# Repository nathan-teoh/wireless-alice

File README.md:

# Wireless Alice

## I have no idea what i'm doing borther

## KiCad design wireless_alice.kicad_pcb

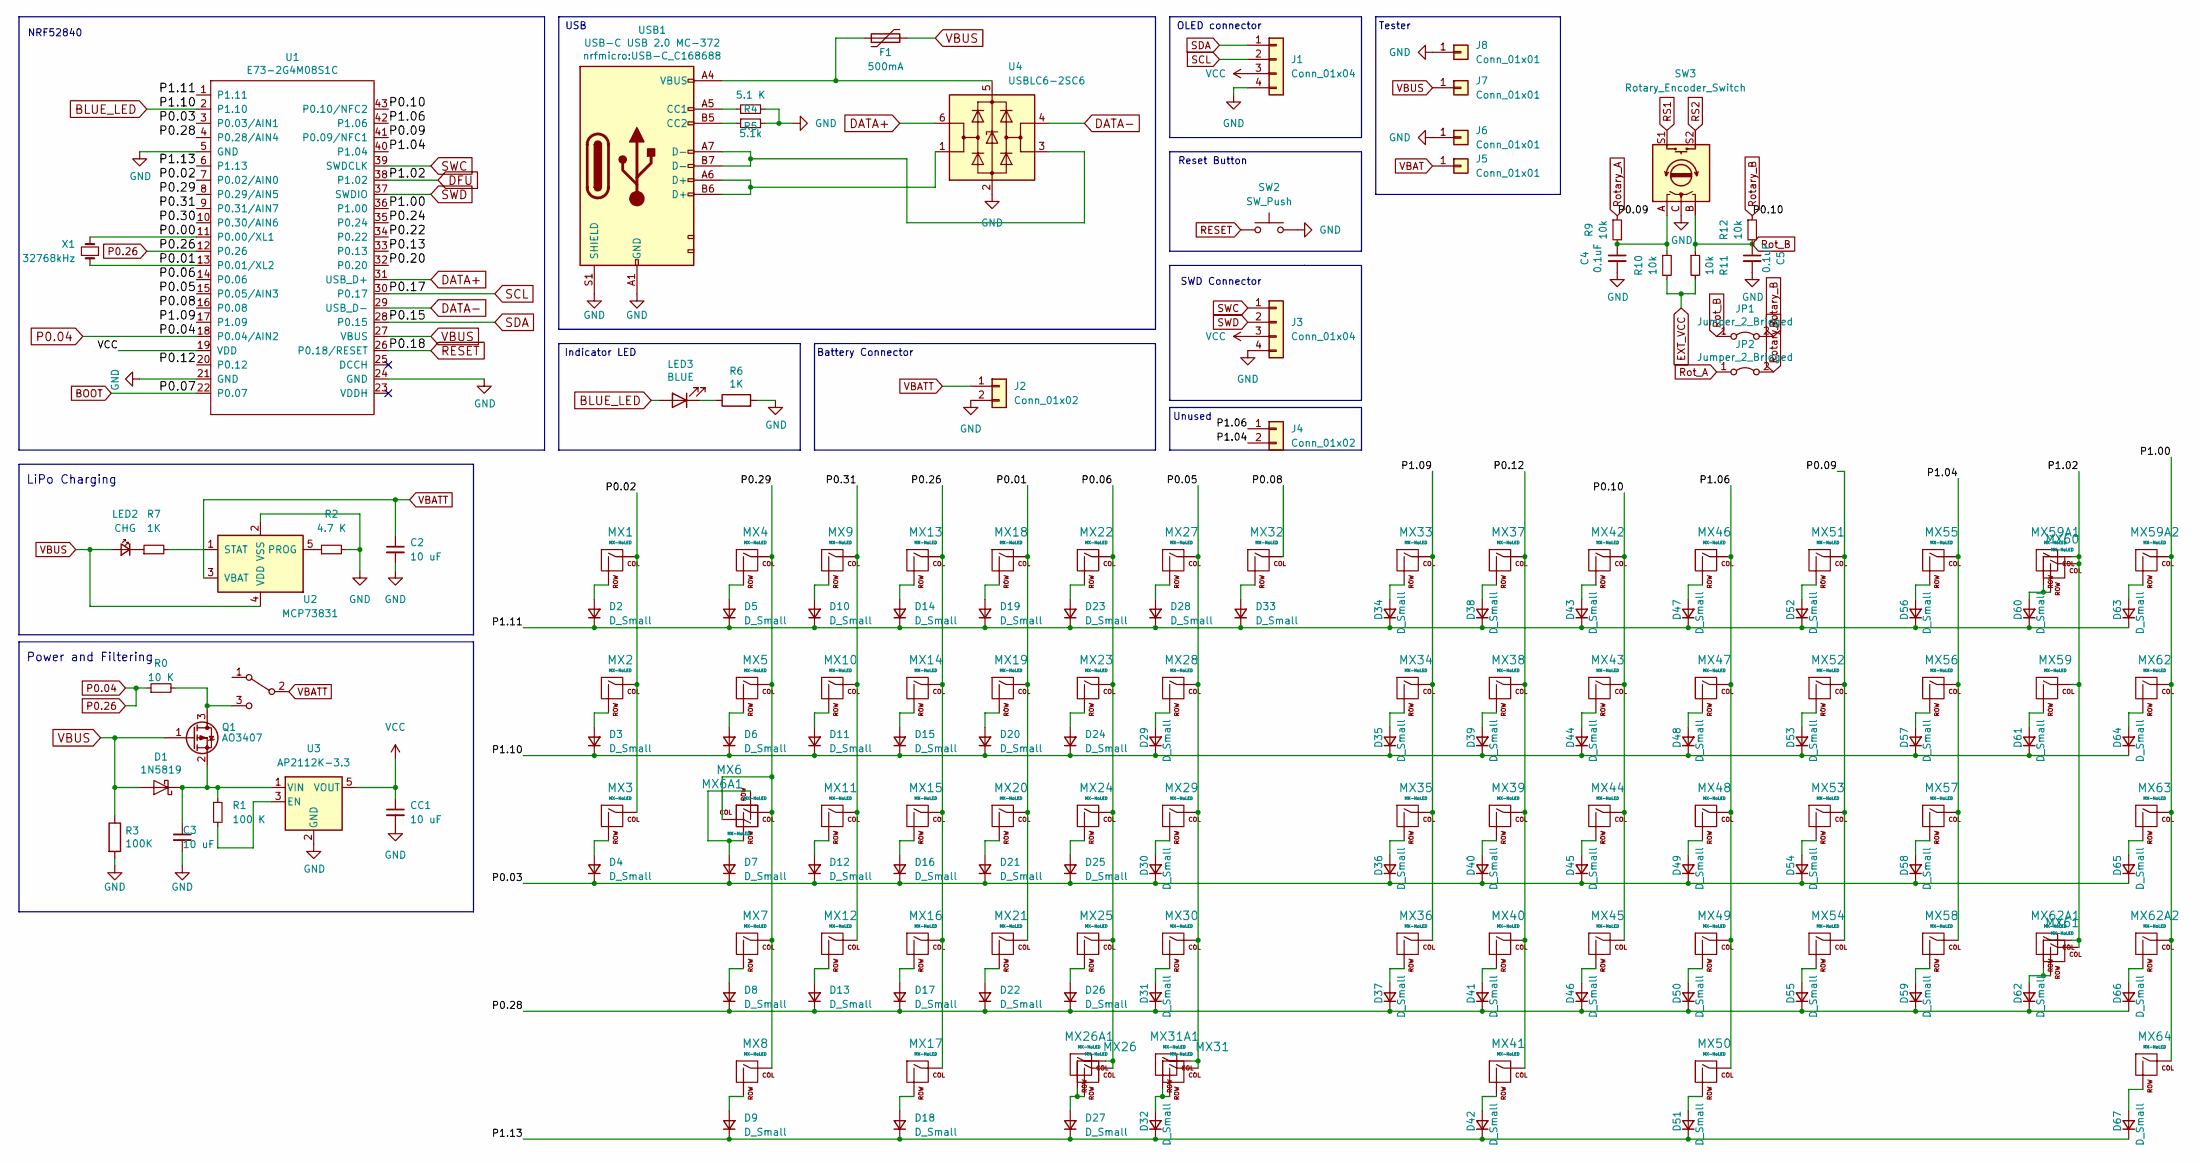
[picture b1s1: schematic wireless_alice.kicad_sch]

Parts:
C2, C3: 10 uF; C_Axial_L3.8mm_D2.6mm_P7.50mm_Horizontal
C4: 0.1uF; CP_Axial_L11.0mm_D6.0mm_P18.00mm_Horizontal; LCSC C49678
C5: 0.1uF; C_0805_2012Metric_Pad1.15x1.40mm_HandSolder; LCSC C49678
CC1: 10 uF; C_Axial_L3.8mm_D2.6mm_P7.50mm_Horizontal
D1: 1N5819; D_SOD-323F
D2, D3, D4, D5, D6, D7, D8, D9, D10, D11, D12, D13, D14, D15, D16, D17, D18, D19, D20, D21, D22, D23, D24, D25, D26, D27, D28, D29, D30, D31, D32, D33, D34, D35, D36, D37, D38, D39, D40, D41, D42, D43, D44, D45, D46, D47, D48, D49, D50, D51, D52, D53, D54, D55, D56, D57, D58, D59, D60, D61, D62, D63, D64, D65, D66, D67: D_Small; D_5W_P12.70mm_Horizontal
F1: 500mA; JST_EH_S4B-EH_1x04_P2.50mm_Horizontal
J1, J3: Conn_01x04; JST_EH_S4B-EH_1x04_P2.50mm_Horizontal
J2, J4: Conn_01x02; JST_EH_S2B-EH_1x02_P2.50mm_Horizontal
J5, J6, J7, J8: Conn_01x01; JST_ACH_BM01B-ACHSS-A-GAN-ETF_1x01-1MP_P1.20mm_Vertical
JP1, JP2: Jumper_2_Bridged; Jumper
LED2: CHG; LED_D3.0mm_Clear
LED3: BLUE; LED_0603_1608Metric
MX1, MX2, MX3, MX4, MX9, MX10, MX11, MX12, MX13, MX14, MX15, MX16, MX18, MX19, MX20, MX21, MX22, MX23, MX24, MX25, MX27, MX28, MX29, MX30, MX31A1, MX32, MX33, MX34, MX35, MX36, MX37, MX38, MX39, MX40, MX42, MX43, MX44, MX45, MX46, MX47, MX48, MX49, MX51, MX52, MX53, MX54, MX55, MX56, MX57, MX58, MX59, MX59A2, MX60, MX62, MX62A2: MX-NoLED; SW_Cherry_MX_1.00u_PCB
MX5, MX8, MX17, MX50, MX64: MX-NoLED; SW_Cherry_MX_1.50u_PCB
MX6, MX6A1, MX62A1: MX-NoLED; SW_Cherry_MX_1.75u_PCB
MX7, MX41, MX61: MX-NoLED; SW_Cherry_MX_2.75u_PCB
MX26: MX-NoLED; SW_Cherry_MX_2.25u_PCB
MX26A1, MX59A1: MX-NoLED; SW_Cherry_MX_2.00u_PCB
MX31: MX-NoLED; SW_Cherry_MX_1.25u_PCB
MX63: MX-NoLED; SW_Cherry_MX_2.25u_PCB_Flipped
Q1: AO3407; SOT-23
R0: 10 K; R_Axial_DIN0614_L14.3mm_D5.7mm_P25.40mm_Horizontal
R1: 100 K; R_Axial_DIN0614_L14.3mm_D5.7mm_P25.40mm_Horizontal
R2: 4.7 K; R_Axial_DIN0614_L14.3mm_D5.7mm_P25.40mm_Horizontal
R3: 100K; R_0603_1608Metric
R4: 5.1 K; R_Axial_DIN0614_L14.3mm_D5.7mm_P25.40mm_Horizontal
R5: 5.1k; R_Axial_DIN0614_L14.3mm_D5.7mm_P25.40mm_Horizontal
R6: 1K; R_0603_1608Metric
R7: 1K; R_Axial_DIN0614_L14.3mm_D5.7mm_P25.40mm_Horizontal
R9, R10, R11, R12: 10k; R_0603_1608Metric_Pad1.05x0.95mm_HandSolder; LCSC C25804
SW1: SW_SPDT; SW_CuK_OS102011MA1QN1_SPDT_Angled
SW2: SW_Push; SW_PUSH_6mm_H4.3mm
SW3: Rotary_Encoder_Switch; RotaryEncoder_Alps_EC11E-Switch_Vertical_H20mm; LCSC C470748
U1: E73-2G4M08S1C; E73-2G4M08S1C-52840
U2: MCP73831; SOT-23-5
U3: AP2112K-3.3; SOT-23-5
U4: USBLC6-2SC6; SOT-23-6
USB1: USB-C USB 2.0 MC-372; USB-C_C168688
X1: 32768kHz; Crystal_SMD_EuroQuartz_EQ161-2Pin_3.2x1.5mm_HandSoldering

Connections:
/P0.00: U1.11 (P0.00/XL1), X1.2
/P0.01: MX18.1 (COL), MX19.1 (COL), MX20.1 (COL), MX21.1 (COL), U1.13 (P0.01/XL2), X1.1
/P0.02: MX1.1 (COL), MX2.1 (COL), MX3.1 (COL), U1.7 (P0.02/AIN0)
/P0.03: D4.1 (K), D7.1 (K), D12.1 (K), D16.1 (K), D21.1 (K), D25.1 (K), D30.1 (K), D36.1 (K), D40.1 (K), D45.1 (K), D49.1 (K), D54.1 (K), D58.1 (K), D65.1 (K), U1.3 (P0.03/AIN1)
/P0.05: MX27.1 (COL), MX28.1 (COL), MX29.1 (COL), MX30.1 (COL), MX31.1 (COL), MX31A1.1 (COL), U1.15 (P0.05/AIN3)
/P0.06: MX22.1 (COL), MX23.1 (COL), MX24.1 (COL), MX25.1 (COL), MX26.1 (COL), MX26A1.1 (COL), U1.14 (P0.06)
/P0.08: MX32.1 (COL), U1.16 (P0.08)
/P0.12: MX37.1 (COL), MX38.1 (COL), MX39.1 (COL), MX40.1 (COL), MX41.1 (COL), U1.20 (P0.12)
/P0.13: U1.33 (P0.13)
/P0.20: U1.32 (P0.20)
/P0.22: U1.34 (P0.22)
/P0.24: U1.35 (P0.24)
/P0.28: D8.1 (K), D13.1 (K), D17.1 (K), D22.1 (K), D26.1 (K), D31.1 (K), D37.1 (K), D41.1 (K), D46.1 (K), D50.1 (K), D55.1 (K), D59.1 (K), D62.1 (K), D66.1 (K), U1.4 (P0.28/AIN4)
/P0.29: MX4.1 (COL), MX5.1 (COL), MX6.1 (COL), MX6A1.1 (COL), MX7.1 (COL), MX8.1 (COL), U1.8 (P0.29/AIN5)
/P0.30: U1.10 (P0.30/AIN6)
/P0.31: MX9.1 (COL), MX10.1 (COL), MX11.1 (COL), MX12.1 (COL), U1.9 (P0.31/AIN7)
/P1.00: MX59A2.1 (COL), MX62.1 (COL), MX62A2.1 (COL), MX63.1 (COL), MX64.1 (COL), U1.36 (P1.00)
/P1.04: J4.2, MX55.1 (COL), MX56.1 (COL), MX57.1 (COL), MX58.1 (COL), U1.40 (P1.04)
/P1.06: J4.1, MX46.1 (COL), MX47.1 (COL), MX48.1 (COL), MX49.1 (COL), MX50.1 (COL), U1.42 (P1.06)
/P1.09: MX33.1 (COL), MX34.1 (COL), MX35.1 (COL), MX36.1 (COL), U1.17 (P1.09)
/P1.11: D2.1 (K), D5.1 (K), D10.1 (K), D14.1 (K), D19.1 (K), D23.1 (K), D28.1 (K), D33.1 (K), D34.1 (K), D38.1 (K), D43.1 (K), D47.1 (K), D52.1 (K), D56.1 (K), D60.1 (K), D63.1 (K), U1.1 (P1.11)
/P1.13: D9.1 (K), D18.1 (K), D27.1 (K), D32.1 (K), D42.1 (K), D51.1 (K), D67.1 (K), U1.6 (P1.13)
BLUE_LED: D3.1 (K), D6.1 (K), D11.1 (K), D15.1 (K), D20.1 (K), D24.1 (K), D29.1 (K), D35.1 (K), D39.1 (K), D44.1 (K), D48.1 (K), D53.1 (K), D57.1 (K), D61.1 (K), D64.1 (K), LED3.2 (A), U1.2 (P1.10)
BOOT: U1.22 (P0.07)
DATA+: U1.31 (USB_D+), U4.6 (I/O1)
DATA-: U1.29 (USB_D-), U4.4 (I/O2)
DFU: MX59.1 (COL), MX59A1.1 (COL), MX60.1 (COL), MX61.1 (COL), MX62A1.1 (COL), U1.38 (P1.02)
GND: C2.2, C3.2, C4.2, C5.2, CC1.2, J1.4, J2.2, J3.4, J6.1, J8.1, R2.2, R3.2, R4.2, R5.2, R6.2, SW2.2, SW3.C, U1.5 (GND), U1.21 (GND), U1.24 (GND), U2.2 (VSS), U3.2 (GND), U4.2 (GND), USB1.A1 (GND), USB1.S1 (SHIELD)
unnamed: C3.1, D1.1 (K), Q1.2 (S), R1.1, U3.1 (VIN)
unnamed: C4.1, R9.2, R10.1, SW3.A
unnamed: D2.2 (A), MX1.2 (ROW)
unnamed: D3.2 (A), MX2.2 (ROW)
unnamed: D4.2 (A), MX3.2 (ROW)
unnamed: D5.2 (A), MX4.2 (ROW)
unnamed: D6.2 (A), MX5.2 (ROW)
unnamed: D7.2 (A), MX6.2 (ROW), MX6A1.2 (ROW)
unnamed: D8.2 (A), MX7.2 (ROW)
unnamed: D9.2 (A), MX8.2 (ROW)
unnamed: D10.2 (A), MX9.2 (ROW)
unnamed: D11.2 (A), MX10.2 (ROW)
unnamed: D12.2 (A), MX11.2 (ROW)
unnamed: D13.2 (A), MX12.2 (ROW)
unnamed: D14.2 (A), MX13.2 (ROW)
unnamed: D15.2 (A), MX14.2 (ROW)
unnamed: D16.2 (A), MX15.2 (ROW)
unnamed: D17.2 (A), MX16.2 (ROW)
unnamed: D18.2 (A), MX17.2 (ROW)
unnamed: D19.2 (A), MX18.2 (ROW)
unnamed: D20.2 (A), MX19.2 (ROW)
unnamed: D21.2 (A), MX20.2 (ROW)
unnamed: D22.2 (A), MX21.2 (ROW)
unnamed: D23.2 (A), MX22.2 (ROW)
unnamed: D24.2 (A), MX23.2 (ROW)
unnamed: D25.2 (A), MX24.2 (ROW)
unnamed: D26.2 (A), MX25.2 (ROW)
unnamed: D27.2 (A), MX26.2 (ROW), MX26A1.2 (ROW)
unnamed: D28.2 (A), MX27.2 (ROW)
unnamed: D29.2 (A), MX28.2 (ROW)
unnamed: D30.2 (A), MX29.2 (ROW)
unnamed: D31.2 (A), MX30.2 (ROW)
unnamed: D32.2 (A), MX31.2 (ROW), MX31A1.2 (ROW)
unnamed: D33.2 (A), MX32.2 (ROW)
unnamed: D34.2 (A), MX33.2 (ROW)
unnamed: D35.2 (A), MX34.2 (ROW)
unnamed: D36.2 (A), MX35.2 (ROW)
unnamed: D37.2 (A), MX36.2 (ROW)
unnamed: D38.2 (A), MX37.2 (ROW)
unnamed: D39.2 (A), MX38.2 (ROW)
unnamed: D40.2 (A), MX39.2 (ROW)
unnamed: D41.2 (A), MX40.2 (ROW)
unnamed: D42.2 (A), MX41.2 (ROW)
unnamed: D43.2 (A), MX42.2 (ROW)
unnamed: D44.2 (A), MX43.2 (ROW)
unnamed: D45.2 (A), MX44.2 (ROW)
unnamed: D46.2 (A), MX45.2 (ROW)
unnamed: D47.2 (A), MX46.2 (ROW)
unnamed: D48.2 (A), MX47.2 (ROW)
unnamed: D49.2 (A), MX48.2 (ROW)
unnamed: D50.2 (A), MX49.2 (ROW)
unnamed: D51.2 (A), MX50.2 (ROW)
unnamed: D52.2 (A), MX51.2 (ROW)
unnamed: D53.2 (A), MX52.2 (ROW)
unnamed: D54.2 (A), MX53.2 (ROW)
unnamed: D55.2 (A), MX54.2 (ROW)
unnamed: D56.2 (A), MX55.2 (ROW)
unnamed: D57.2 (A), MX56.2 (ROW)
unnamed: D58.2 (A), MX57.2 (ROW)
unnamed: D59.2 (A), MX58.2 (ROW)
unnamed: D60.2 (A), MX59A1.2 (ROW), MX60.2 (ROW)
unnamed: D61.2 (A), MX59.2 (ROW)
unnamed: D62.2 (A), MX61.2 (ROW), MX62A1.2 (ROW)
unnamed: D63.2 (A), MX59A2.2 (ROW)
unnamed: D64.2 (A), MX62.2 (ROW)
unnamed: D65.2 (A), MX63.2 (ROW)
unnamed: D66.2 (A), MX62A2.2 (ROW)
unnamed: D67.2 (A), MX64.2 (ROW)
unnamed: F1.1, U4.5 (VBUS), USB1.A4 (VBUS)
unnamed: LED2.1 (K), R7.1
unnamed: LED3.1 (K), R6.1
unnamed: Q1.3 (D), R0.2, SW1.3 (C)
unnamed: R1.2, U3.3 (EN)
unnamed: R2.1, U2.5 (PROG)
unnamed: R4.1, USB1.A5 (CC1)
unnamed: R5.1, USB1.B5 (CC2)
unnamed: R7.2, U2.1 (STAT)
unnamed: R10.2, R11.2
unnamed: U4.1 (I/O1), USB1.A6 (D+), USB1.B6 (D+)
unnamed: U4.3 (I/O2), USB1.A7 (D-), USB1.B7 (D-)
P0.04: MX13.1 (COL), MX14.1 (COL), MX15.1 (COL), MX16.1 (COL), MX17.1 (COL), R0.1, U1.12 (P0.26), U1.18 (P0.04/AIN2)
RESET: SW2.1, U1.26 (P0.18/RESET)
RS1: SW3.S1
RS2: SW3.S2
Rot_B: C5.1, JP1.1 (A), R11.1, R12.2, SW3.B
Rotary_A: JP2.2 (B), MX51.1 (COL), MX52.1 (COL), MX53.1 (COL), MX54.1 (COL), R9.1, U1.41 (P0.09/NFC1)
Rotary_B: JP1.2 (B), MX42.1 (COL), MX43.1 (COL), MX44.1 (COL), MX45.1 (COL), R12.1, U1.43 (P0.10/NFC2)
SCL: J1.2, U1.30 (P0.17)
SDA: J1.1, U1.28 (P0.15)
SWC: J3.1, U1.39 (SWDCLK)
SWD: J3.2, U1.37 (SWDIO)
VBAT: J5.1
VBATT: C2.1, J2.1, SW1.2 (B), U2.3 (VBAT)
VBUS: D1.2 (A), F1.2, J7.1, LED2.2 (A), Q1.1 (G), R3.1, U1.27 (VBUS), U2.4 (VDD)
VCC: CC1.1, J1.3, J3.3, U1.19 (VDD), U3.5 (VOUT)

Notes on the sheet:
NRF52840
Tester
Battery Connector
Power and Filtering
LiPo Charging
Reset Button
USB
OLED connector
SWD Connector
Indicator LED
Unused

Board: 2 copper layers, 171 parts (1 on the bottom side), 112 nets, no tracks yet.

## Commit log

2022-08-24 first
2022-08-24 add readme
2022-08-30 More pcb refinement
2022-09-29 more progress my guy
